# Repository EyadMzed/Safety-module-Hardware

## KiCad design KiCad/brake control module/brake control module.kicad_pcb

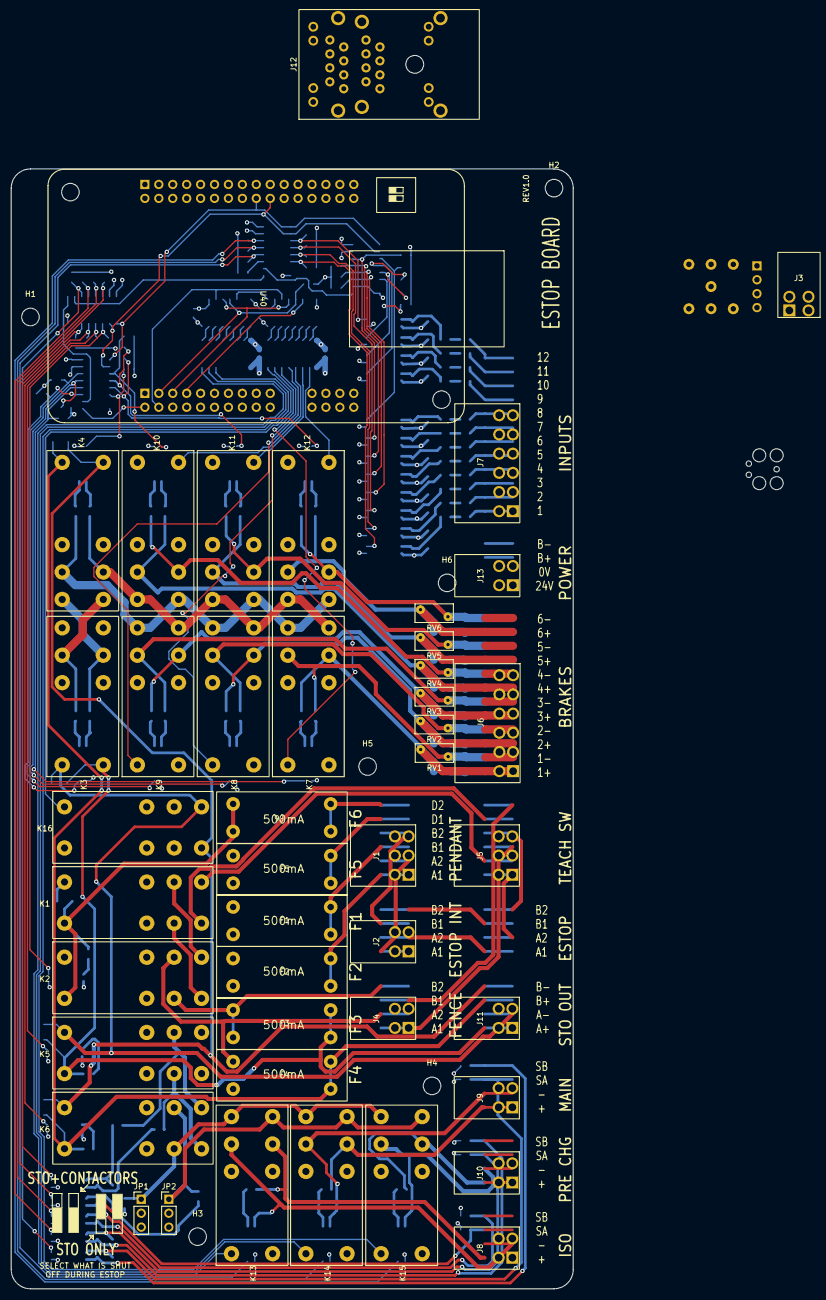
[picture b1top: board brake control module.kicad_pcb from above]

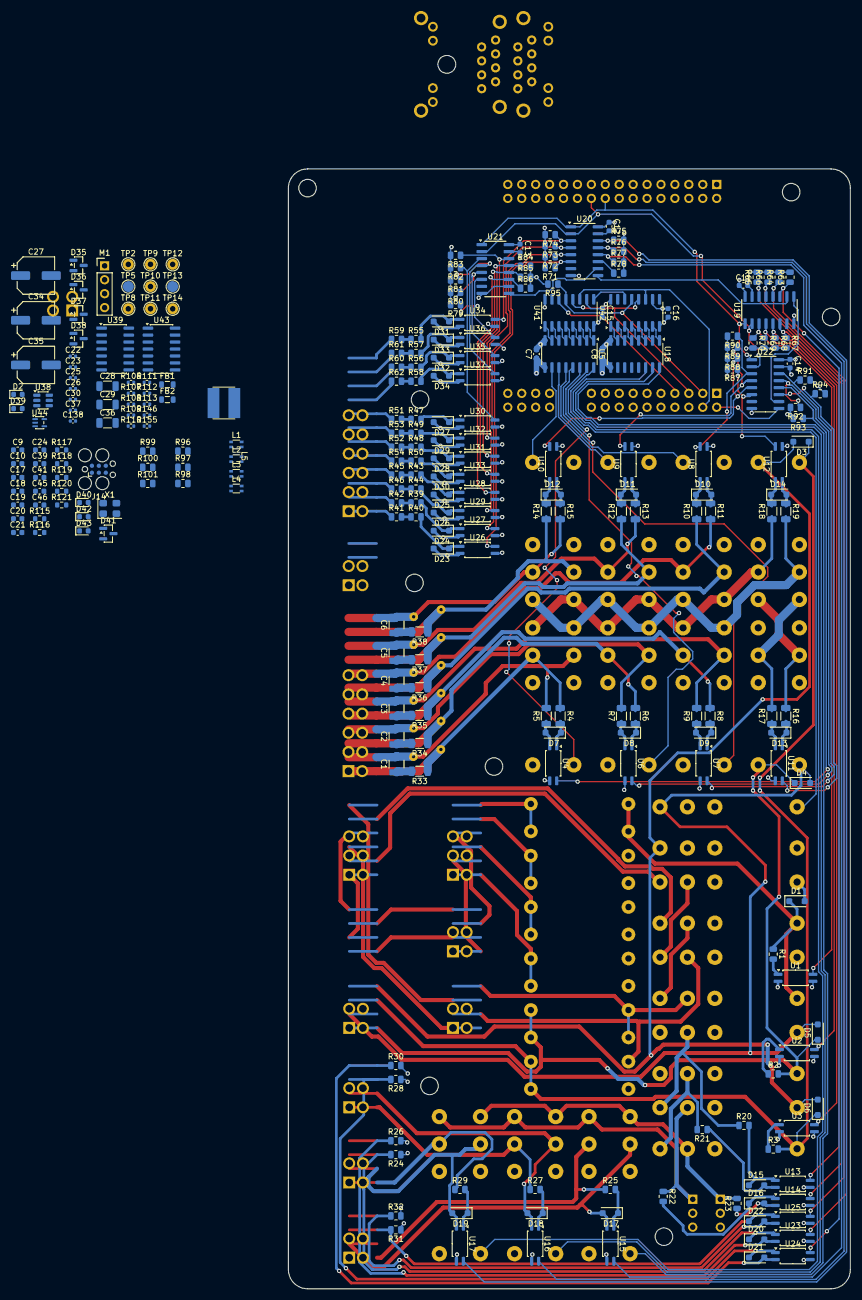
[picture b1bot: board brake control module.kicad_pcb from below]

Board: 4 copper layers, 102.5 x 204.2 mm, 312 parts (262 on the bottom side), 236 nets.

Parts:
C1, C2, C3, C4, C5, C6: .47uf; C_1210_3225Metric
C7, C8, C11, C12, C13, C14, C15, C16: 1uf; C_0603_1608Metric
C9, C17: 4.7uf; C_0603_1608Metric
C10, C18, C19, C21, C24, C39, C41, C45, C46: .1uf; C_0603_1608Metric
C20: 2.2uf; C_0603_1608Metric
C22, C23, C25, C26, C37, C138: .1uf; C_0402_1005Metric
C27, C34, C35: 22uf; CP_Elec_6.3x5.9
C28, C29: 22uf; C_1206_3216Metric
C30: 75pf; C_0402_1005Metric
C36: 2.2uf; C_1206_3216Metric
D1, D3, D4, D5, D6, D7, D8, D9, D10, D11, D12, D13, D14, D15, D16, D17, D18, D19, D20, D21, D22, D23, D24, D25, D26, D27, D28, D29, D30, D31, D32, D33, D34: D; D_SOD-123F
D2, D39, D40, D42, D43: LED; LED_0603_1608Metric
D35, D36, D37, D38: SM712; SOT-23
D41: BAT54SLT1G; SOT-23
F1, F2, F3, F4, F5, F6: Fuse; 5x20mm fuse
FB1, FB2: 0; L_0805_2012Metric
H1, H2, H3, H4, H5, H6: MountingHole; MountingHole_3.2mm_M3
J1: PENDANT ESTOP + DMS; 2x03_P3.5_KF2EDGSR
J2: ESTOP CONTROLLER; 2x02_P3.5_KF2EDGSR
J3: ESTOP EXTERNAL; 2x02_P3.5_KF2EDGSR
J4: FENCE; 2x02_P3.5_KF2EDGSR
J5: TEACH SWITCH; 2x03_P3.5_KF2EDGSR
J6: BRAKES; 2x06_P3.5_KF2EDGSR
J7: INPUTS; 2x06_P3.5_KF2EDGSR
J8: ISO_CONTACTOR; 2x02_P3.5_KF2EDGSR
J9: MAIN_CONTACTOR; 2x02_P3.5_KF2EDGSR
J10: PRECHARGE_CONTACTOR; 2x02_P3.5_KF2EDGSR
J11: STO OUT; 2x02_P3.5_KF2EDGSR
J12: 8P8C_LED_Shielded_x2; RJ45_XDRJ-1609-002
J13: POWER; 2x02_P3.5_KF2EDGSR
J14: Conn_ARM_SWD_TagConnect_TC2030; Tag-Connect_TC2030-IDC-FP_2x03_P1.27mm_Vertical
JP1, JP2: Jumper_2_Open; PinHeader_1x03_P2.54mm_Vertical
K1, K2, K3, K4, K5, K6, K7, K8, K9, K10, K11, K12, K13, K14, K15, K16: Relay_DPDT; az733 form C
L1, L2, L3, L4: L_Ferrite_Coupled; SMD-4P,2x1.2mm
L5: 15uH; CY54_INDUCTOR
M1: Fan_4pin; PinHeader_1x04_P2.54mm_Vertical
R1, R2, R3, R20, R21, R22, R23, R24, R25, R26, R27, R28, R29, R30, R31, R32, R39, R40, R41, R42, R43, R44, R45, R46, R47, R48, R49, R50, R51, R52, R53, R54, R55, R56, R57, R58, R59, R60, R61, R62, R96, R97, R98, R99, R100, R101: 9.1k; R_0805_2012Metric
R4, R5, R6, R7, R8, R9, R10, R11, R12, R13, R14, R15, R16, R17, R18, R19: 33k; R_1206_3216Metric
R33, R34, R35, R36, R37, R38: 470; R_1206_3216Metric
R63, R64, R65, R66, R67, R68, R69, R70, R71, R72, R73, R74, R75, R76, R77, R78, R79, R80, R81, R82, R83, R84, R85, R86, R87, R88, R89, R90, R91, R92, R93, R94: 1.5k; R_0805_2012Metric
R95: 220k; R_0805_2012Metric
R106, R146: 10k; R_0402_1005Metric
R107: 560k; R_0402_1005Metric
R108, R111: 100k; R_0402_1005Metric
R109, R110: 120; R_0402_1005Metric
R112: 22.1k; R_0402_1005Metric
R113: 1k; R_0402_1005Metric
R115, R120: 10k; R_0603_1608Metric
R116, R117, R118, R119, R121: 1k; R_0603_1608Metric
R155: 0; R_0402_1005Metric
RV1, RV2, RV3, RV4, RV5, RV6: Varistor; RV_Disc_D7mm_W3.4mm_P5mm
TP2, TP8, TP9, TP10, TP11, TP12, TP14: GND; TestPoint_THTPad_D2.0mm_Drill1.0mm
TP5: 5V_ISO; TestPoint_Pad_D2.0mm
TP13: 24V_ISO; TestPoint_Pad_D2.0mm
U1, U2, U3, U4, U6, U7, U8, U9, U10, U11, U12, U13, U14, U15, U16, U17, U23, U24, U25, U26, U27, U28, U29, U30, U31, U32, U33, U34, U35, U36, U37: 140357145400; SOP-4_4.4x2.6mm_P1.27mm
U5, U18: ULN2003; SOIC-16_3.9x9.9mm_P1.27mm
U19, U20, U21, U22: 74HC165; SOIC-16_3.9x9.9mm_P1.27mm
U38: TPS54202DDC; SOT-23-6
U39, U43: SP3491EEN-L/TR; SOIC-14_3.9x8.7mm_P1.27mm
U40: STM32F413RGT6; EM_serial_module
U41, U42: 74HC595; SOIC-16_3.9x9.9mm_P1.27mm
U44: 74LVC1G126; SOT-353_SC-70-5
X1: 25 MHz VCXO; Oscillator_SMD_SeikoEpson_SG8002CE-4Pin_3.2x2.5mm

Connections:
0V_CHAIN_A: D4.2 (A), D5.2 (A), J11.2, K3.8, K5.8, K16.5
0V_CHAIN_B: D3.2 (A), D6.2 (A), J11.4, K4.8, K6.8, K16.4
+3.3V: C11.1, C12.1, C13.1, C14.1, C15.1, C16.1, C17.1, C18.1, C19.1, C22.1, C23.1, C24.1, C28.2, C29.2, C30.2, C39.1, C41.1, C46.2, C138.1, D41.2 (K), J14.1 (VCC), L5.2, R63.2, R64.2, R65.2, R66.2, R67.2, R68.2, R69.2, R70.2, R71.2, R72.2, R73.2, R74.2, R75.2, R76.2, R77.2, R78.2, R79.2, R80.2, R81.2, R82.2, R83.2, R84.2, R85.2, R86.2, R87.2, R88.2, R89.2, R90.2, R91.2, R92.2, R93.2, R94.2, R95.2, R111.2, R113.2, R118.1, R146.2, TP5.1 (1_1), U19.16 (VCC), U20.16 (VCC), U21.16 (VCC), U22.16 (VCC), U39.4 (DE), U39.13 (VCC), U39.14 (VCC), U41.10 (~SRCLR), U41.16 (VCC), U42.10 (~SRCLR), U42.16 (VCC), U43.13 (VCC), U43.14 (VCC), U44.5 (VCC), X1.4 (Vcc)
+24V: C7.1, C8.1, C26.2, C27.1, C34.1, C36.2, FB1.1, K7.1, K8.1, K9.1, K10.1, K11.1, K12.1, K13.1, K14.1, K15.1, K16.1, R106.2, R107.2, R155.2, TP13.1 (1_1), U5.9 (COM), U18.9 (COM), U38.3 (VIN)
+24V_2: F1.1, F2.1, F5.1, J13.1, JP2.2 (B), K5.5, R24.1, R28.1, R31.1, R120.1
+24V_CHAIN_A: D4.1 (K), D5.1 (K), F3.2, J11.1, K3.1, K5.1, R3.1
+24V_CHAIN_B: D3.1 (K), D6.1 (K), F4.2, J11.3, K4.1, K6.1, R101.1
/Aux Inputs/INPUT_1: R71.1, U20.6 (D7), U26.4
/Aux Inputs/INPUT_2: R72.1, U20.5 (D6), U27.4
/Aux Inputs/INPUT_3: R73.1, U20.4 (D5), U29.4
/Aux Inputs/INPUT_4: R86.1, U21.11 (D0), U28.4
/Aux Inputs/INPUT_5: R85.1, U21.12 (D1), U33.4
/Aux Inputs/INPUT_6: R84.1, U21.13 (D2), U31.4
/Aux Inputs/INPUT_7: R83.1, U21.14 (D3), U32.4
/Aux Inputs/INPUT_8: R82.1, U21.3 (D4), U30.4
/Aux Inputs/INPUT_9: R81.1, U21.4 (D5), U37.4
/Aux Inputs/INPUT_10: R80.1, U21.5 (D6), U35.4
/Aux Inputs/INPUT_11: R79.1, U21.6 (D7), U36.4
/Aux Inputs/INPUT_12: R74.1, U20.3 (D4), U34.4
/Brake Outputs/BRAKE_1_RETURN: C1.2, J6.2, K7.3, R4.1, RV1.2
/Brake Outputs/BRAKE_1_SUPPLY: J6.1, K7.6, R5.1, R33.1, RV1.1
/Brake Outputs/BRAKE_2_RETURN: C2.2, J6.4, K8.3, R6.1, RV2.2
/Brake Outputs/BRAKE_2_SUPPLY: J6.3, K8.6, R7.1, R34.1, RV2.1
/Brake Outputs/BRAKE_3_RETURN: C3.2, J6.6, K9.3, R8.1, RV3.2
/Brake Outputs/BRAKE_3_SUPPLY: J6.5, K9.6, R9.1, R35.1, RV3.1
/Brake Outputs/BRAKE_4_RETURN: C4.2, J6.8, K10.3, R10.1, RV4.2
/Brake Outputs/BRAKE_4_SUPPLY: J6.7, K10.6, R11.1, R36.1, RV4.1
/Brake Outputs/BRAKE_5_RETURN: C5.2, J6.10, K11.3, R12.1, RV5.2
/Brake Outputs/BRAKE_5_SUPPLY: J6.9, K11.6, R13.1, R37.1, RV5.1
/Brake Outputs/BRAKE_6_RETURN: C6.2, J6.12, K12.3, R14.1, RV6.2
/Brake Outputs/BRAKE_6_SUPPLY: J6.11, K12.6, R15.1, R38.1, RV6.1
/Brake Relays and Feedback/BRK_1_FBK: R93.1, U4.4, U22.12 (D1)
/Brake Relays and Feedback/BRK_2_FBK: R92.1, U6.4, U22.13 (D2)
/Brake Relays and Feedback/BRK_3_FBK: R91.1, U7.4, U22.14 (D3)
/Brake Relays and Feedback/BRK_4_FBK: R90.1, U8.4, U22.3 (D4)
/Brake Relays and Feedback/BRK_5_FBK: R89.1, U9.4, U22.4 (D5)
/Brake Relays and Feedback/BRK_6_FBK: R88.1, U10.4, U22.5 (D6)
/Brake Relays and Feedback/BRK_A_FBK: R94.1, U11.4, U22.11 (D0)
/Brake Relays and Feedback/BRK_B_FBK: R87.1, U12.4, U22.6 (D7)
/Brake Relays and Feedback/BRK_RELAY_1: K7.8, U5.15 (O2)
/Brake Relays and Feedback/BRK_RELAY_2: K8.8, U5.14 (O3)
/Brake Relays and Feedback/BRK_RELAY_3: K9.8, U5.13 (O4)
/Brake Relays and Feedback/BRK_RELAY_4: K10.8, U5.12 (O5)
/Brake Relays and Feedback/BRK_RELAY_5: K11.8, U5.11 (O6)
/Brake Relays and Feedback/BRK_RELAY_6: K12.8, U5.10 (O7)
/Brake Relays and Feedback/INT_BRAKE_RETURN: K4.3, K7.5, K8.5, K9.5, K10.5, K11.5, K12.5, R19.1
/Brake Relays and Feedback/INT_BRAKE_SUPPLY: K4.6, K7.4, K8.4, K9.4, K10.4, K11.4, K12.4, R17.1
/Communication/FAN_TACH_ISO: C37.1, R146.1
/Communication/RX: U39.2 (RO), U43.5 (DI)
/Communication/TX_PASSTHROUGH_ENABLE: U43.3 (~RE), U44.1
/Communication/TX_SNOOP: U39.5 (DI), U43.2 (RO), U44.4
/Contactor Relays and Feedback/CHAIN_A_RELAY_FBK: R67.1, U13.4, U19.6 (D7)
/Contactor Relays and Feedback/CHAIN_B_RELAY_FBK: R65.1, U14.4, U19.14 (D3)
/Contactor Relays and Feedback/ISO_CONTACTOR_RETURN: J8.2, K13.6, R96.2
/Contactor Relays and Feedback/ISO_CONTACTOR_SUPPLY: J8.1, K13.3, R25.2
/Contactor Relays and Feedback/ISO_CON_FBK: R77.1, U15.4, U20.12 (D1)
/Contactor Relays and Feedback/ISO_CON_FBK_EXT: R66.1, U19.13 (D2), U25.4
/Contactor Relays and Feedback/ISO_CON_FBK_EXT_A: D22.1 (K), J8.3, R31.2, U25.1
/Contactor Relays and Feedback/ISO_CON_FBK_EXT_B: D22.2 (A), J8.4, R32.1, U25.2
/Contactor Relays and Feedback/ISO_CON_RELAY: K13.8, U18.14 (O3)
/Contactor Relays and Feedback/MAIN_CONTACTOR_RETURN: J9.2, K14.6, R29.2
/Contactor Relays and Feedback/MAIN_CONTACTOR_SUPPLY: J9.1, K14.3, R27.2
/Contactor Relays and Feedback/MAIN_CON_FBK: R76.1, U16.4, U20.13 (D2)
/Contactor Relays and Feedback/MAIN_CON_FBK_EXT: R63.1, U19.11 (D0), U24.4
/Contactor Relays and Feedback/MAIN_CON_FBK_EXT_A: D21.1 (K), J9.3, R28.2, U24.1
/Contactor Relays and Feedback/MAIN_CON_FBK_EXT_B: D21.2 (A), J9.4, R30.1, U24.2
/Contactor Relays and Feedback/MAIN_CON_RELAY: K14.8, U18.15 (O2)
/Contactor Relays and Feedback/PRECHARGE_CONTACTOR_RETURN: J10.2, K15.6, R98.2
/Contactor Relays and Feedback/PRECHARGE_CONTACTOR_SUPPLY: J10.1, K15.3, R97.2
/Contactor Relays and Feedback/PRE_CON_FBK: R75.1, U17.4, U20.14 (D3)
/Contactor Relays and Feedback/PRE_CON_FBK_EXT: R64.1, U19.12 (D1), U23.4
/Contactor Relays and Feedback/PRE_CON_FBK_EXT_A: D20.1 (K), J10.3, R24.2, U23.1
/Contactor Relays and Feedback/PRE_CON_FBK_EXT_B: D20.2 (A), J10.4, R26.1, U23.2
/Contactor Relays and Feedback/PRE_CON_RELAY: K15.8, U18.16 (O1)
/MCU/24V_SENSE: C21.1, D41.3 (common), R120.2, R121.1
/MCU/NRESET: C10.2, J14.3 (~RESET)
CHAIN_A_FBK: R69.1, U2.4, U19.4 (D5)
CHAIN_B_FBK: R68.1, U3.4, U19.5 (D6)
CHAIN_RELAY: K16.8, U5.16 (O1)
DMS_FBK: R70.1, U1.4, U19.3 (D4)
EXT_BRAKE_RETURN: J13.4, K3.4
EXT_BRAKE_SUPPLY: J13.3, K3.5
GND: C7.2, C8.2, C9.2, C10.1, C11.2, C12.2, C13.2, C14.2, C15.2, C16.2, C17.2, C18.2, C19.2, C20.1, C21.2, C22.2, C23.2, C24.2, C26.1, C27.2, C28.1, C29.1, C34.2, C35.2, C36.1, C37.2, C39.2, C41.2, C45.1, C46.1, C138.2, D2.1 (K), D35.3 (common), D36.3 (common), D37.3 (common), D38.3 (common), D39.1 (K), D40.1 (K), D41.1 (A), D42.1 (K), D43.1 (K), FB2.2, J12.9, J12.11, J12.21, J12.23, J12.SH, J14.5 (GND), M1.1 (-), R108.1, R112.1, R115.1, R121.2, TP2.1 (1_1), TP8.1 (1_1), TP9.1 (1_1), TP10.1 (1_1), TP11.1 (1_1), TP12.1 (1_1), TP14.1 (1_1), U1.3, U2.3, U3.3, U4.3, U5.8 (GND), U6.3, U7.3, U8.3, U9.3, U10.3, U11.3, U12.3, U13.3, U14.3, U15.3, U16.3, U17.3, U18.8 (GND), U19.8 (GND), U19.15 (~CE), U20.8 (GND), U20.15 (~CE), U21.8 (GND), U21.10 (DS), U21.15 (~CE), U22.8 (GND), U22.15 (~CE), U23.3, U24.3, U25.3, U26.3, U27.3, U28.3, U29.3, U30.3, U31.3, U32.3, U33.3, U34.3, U35.3, U36.3, U37.3, U38.1 (GND), U39.3 (~RE), U39.6 (GND), U39.7 (GND), U41.8 (GND), U42.8 (GND), U43.6 (GND), U43.7 (GND), U44.3 (GND), X1.2 (GND)
GND2: D1.2 (A), D23.2 (A), D24.2 (A), D25.2 (A), D26.2 (A), D27.2 (A), D28.2 (A), D29.2 (A), D30.2 (A), D31.2 (A), D32.2 (A), D33.2 (A), D34.2 (A), J13.2, JP1.2 (B), K1.8, K2.8, K5.4, K16.3, K16.6, R26.2, R30.2, R32.2, U1.2, U2.2, U3.2, U26.2, U27.2, U28.2, U29.2, U30.2, U31.2, U32.2, U33.2, U34.2, U35.2, U36.2, U37.2
INPUT_CLK: U19.2 (CP), U20.2 (CP), U21.2 (CP), U22.2 (CP)
INPUT_LOAD: U19.1 (~PL), U20.1 (~PL), U21.1 (~PL), U22.1 (~PL)
unnamed: C1.1, R33.2
unnamed: C2.1, R34.2
unnamed: C3.1, R35.2
unnamed: C4.1, R36.2
unnamed: C5.1, R37.2
unnamed: C6.1, R38.2
unnamed: D1.1 (K), F6.2, K1.1, K2.1, R99.1
unnamed: D2.2 (A), R106.1
unnamed: D7.2 (A), R5.2, U4.2
unnamed: D7.1 (K), R4.2, U4.1
unnamed: D8.2 (A), R7.2, U6.2
unnamed: D8.1 (K), R6.2, U6.1
unnamed: D9.2 (A), R9.2, U7.2
unnamed: D9.1 (K), R8.2, U7.1
unnamed: D10.2 (A), R11.2, U8.2
unnamed: D10.1 (K), R10.2, U8.1
unnamed: D11.2 (A), R13.2, U9.2
unnamed: D11.1 (K), R12.2, U9.1
unnamed: D12.2 (A), R15.2, U10.2
unnamed: D12.1 (K), R14.2, U10.1
unnamed: D13.2 (A), R18.2, U11.2
unnamed: D13.1 (K), R16.2, U11.1
unnamed: D14.2 (A), R19.2, U12.2
unnamed: D14.1 (K), R17.2, U12.1
unnamed: D15.2 (A), R21.1, U13.2
unnamed: D15.1 (K), R20.2, U13.1
unnamed: D16.2 (A), R23.1, U14.2
unnamed: D16.1 (K), R22.2, U14.1
unnamed: D17.2 (A), R96.1, U15.2
unnamed: D17.1 (K), R25.1, U15.1
unnamed: D18.2 (A), R29.1, U16.2
unnamed: D18.1 (K), R27.1, U16.1
unnamed: D19.2 (A), R98.1, U17.2
unnamed: D19.1 (K), R97.1, U17.1
unnamed: D23.1 (K), R40.2, U26.1
unnamed: D24.1 (K), R39.2, U27.1
unnamed: D25.1 (K), R43.2, U28.1
unnamed: D26.1 (K), R44.2, U29.1
unnamed: D27.1 (K), R47.2, U30.1
unnamed: D28.1 (K), R48.2, U31.1
unnamed: D29.1 (K), R49.2, U32.1
unnamed: D30.1 (K), R50.2, U33.1
unnamed: D31.1 (K), R55.2, U34.1
unnamed: D32.1 (K), R56.2, U35.1
unnamed: D33.1 (K), R57.2, U36.1
unnamed: D34.1 (K), R58.2, U37.1
unnamed: D35.1 (A1), J12.6, L1.1
unnamed: D35.2 (A2), J12.3, L1.3
unnamed: D36.1 (A1), J12.16, L3.1
unnamed: D36.2 (A2), J12.17, L3.3
unnamed: D37.1 (A1), J12.4, L2.1
unnamed: D37.2 (A2), J12.5, L2.3
unnamed: D38.1 (A1), J12.18, L4.1
unnamed: D38.2 (A2), J12.15, L4.3
unnamed: D39.2 (A), R113.1
unnamed: D40.2 (A), R118.2
unnamed: D42.2 (A), R116.2
unnamed: D43.2 (A), R117.2
unnamed: FB1.2, J12.1, J12.7, J12.13, J12.19
unnamed: FB2.1, J12.2, J12.8, J12.14, J12.20
unnamed: F2.2, J1.1
unnamed: J1.2, J2.1
unnamed: F1.2, J1.3
unnamed: J1.4, J2.3
unnamed: F5.2, J1.5
unnamed: F6.1, J1.6
unnamed: J2.2, J3.1
unnamed: J2.4, J3.3
unnamed: J3.2, J5.1
unnamed: J3.4, J5.4
unnamed: J4.1, J5.3
unnamed: F4.1, J4.2, K2.6
unnamed: J4.3, J5.6
unnamed: F3.1, J4.4, K2.3
unnamed: J5.2, K1.5
unnamed: J5.5, K1.4
unnamed: J7.1, R41.1
unnamed: J7.2, R42.1
unnamed: J7.3, R46.1
unnamed: J7.4, R45.1
unnamed: J7.5, R54.1
unnamed: J7.6, R52.1
unnamed: J7.7, R53.1
unnamed: J7.8, R51.1
unnamed: J7.9, R62.1
unnamed: J7.10, R60.1
unnamed: J7.11, R61.1
unnamed: J7.12, R59.1
unnamed: JP1.1 (A), K6.3, K13.5, K14.5, K15.5, R23.2
unnamed: JP2.1 (A), K6.6, K13.4, K14.4, K15.4, R22.1
unnamed: K1.3, K2.4
unnamed: K1.6, K2.5
unnamed: K3.3, K4.4, R18.1
unnamed: K3.6, K4.5, R16.1
unnamed: K5.3, K6.4, R21.2
unnamed: K5.6, K6.5, R20.1
unnamed: C35.1, M1.2 (+), R155.1
unnamed: R1.1, R99.2
unnamed: R1.2, U1.1
unnamed: R2.1, R3.2
unnamed: R2.2, U2.1
unnamed: R39.1, R42.2
unnamed: R40.1, R41.2
unnamed: R43.1, R45.2
unnamed: R44.1, R46.2
unnamed: R47.1, R51.2
unnamed: R48.1, R52.2
unnamed: R49.1, R53.2
unnamed: R50.1, R54.2
unnamed: R55.1, R59.2
unnamed: R56.1, R60.2
unnamed: R57.1, R61.2
unnamed: R58.1, R62.2
unnamed: R100.1, R101.2
unnamed: R100.2, U3.1
unnamed: U18.1 (I1), U42.7 (QH)
unnamed: U18.2 (I2), U42.6 (QG)
unnamed: U18.3 (I3), U42.5 (QF)
unnamed: U18.4 (I4), U42.4 (QE)
unnamed: U18.5 (I5), U42.3 (QD)
unnamed: U18.6 (I6), U42.2 (QC)
unnamed: U18.7 (I7), U42.1 (QB)
unnamed: U19.10 (DS), U20.9 (Q7)
unnamed: U19.9 (Q7), U22.10 (DS)
unnamed: R78.1, U20.11 (D0)
unnamed: U20.10 (DS), U21.9 (Q7)
unnamed: C25.1, U38.6 (BOOT)
unnamed: R107.1, R108.2, U38.5 (EN)
unnamed: C30.1, R111.1, R112.2, U38.4 (FB)
unnamed: C25.2, L5.1, U38.2 (SW)
unnamed: L1.4, R109.1, U39.12 (A)
unnamed: L2.4, U39.9 (Y)
unnamed: L1.2, R109.2, U39.11 (~B)
unnamed: L2.2, U39.10 (~Z)
unnamed: U5.7 (I7), U41.1 (QB)
unnamed: U5.6 (I6), U41.2 (QC)
unnamed: U5.5 (I5), U41.3 (QD)
unnamed: U5.4 (I4), U41.4 (QE)
unnamed: U5.3 (I3), U41.5 (QF)
unnamed: U5.2 (I2), U41.6 (QG)
unnamed: U41.9 (QH'), U42.14 (SER)
unnamed: U5.1 (I1), U41.7 (QH)
unnamed: L3.4, R110.1, U43.12 (A)
unnamed: L4.4, U43.9 (Y)
unnamed: L3.2, R110.2, U43.11 (~B)
unnamed: L4.2, U43.10 (~Z)
unnamed: C20.2, C45.2, R119.2, X1.1 (VC)
OUTPUT_CLK: U41.11 (SRCLK), U42.11 (SRCLK)
OUTPUT_ENABLE: R95.1, U41.13 (~OE), U42.13 (~OE)
OUTPUT_WRITE: U41.12 (RCLK), U42.12 (RCLK)
